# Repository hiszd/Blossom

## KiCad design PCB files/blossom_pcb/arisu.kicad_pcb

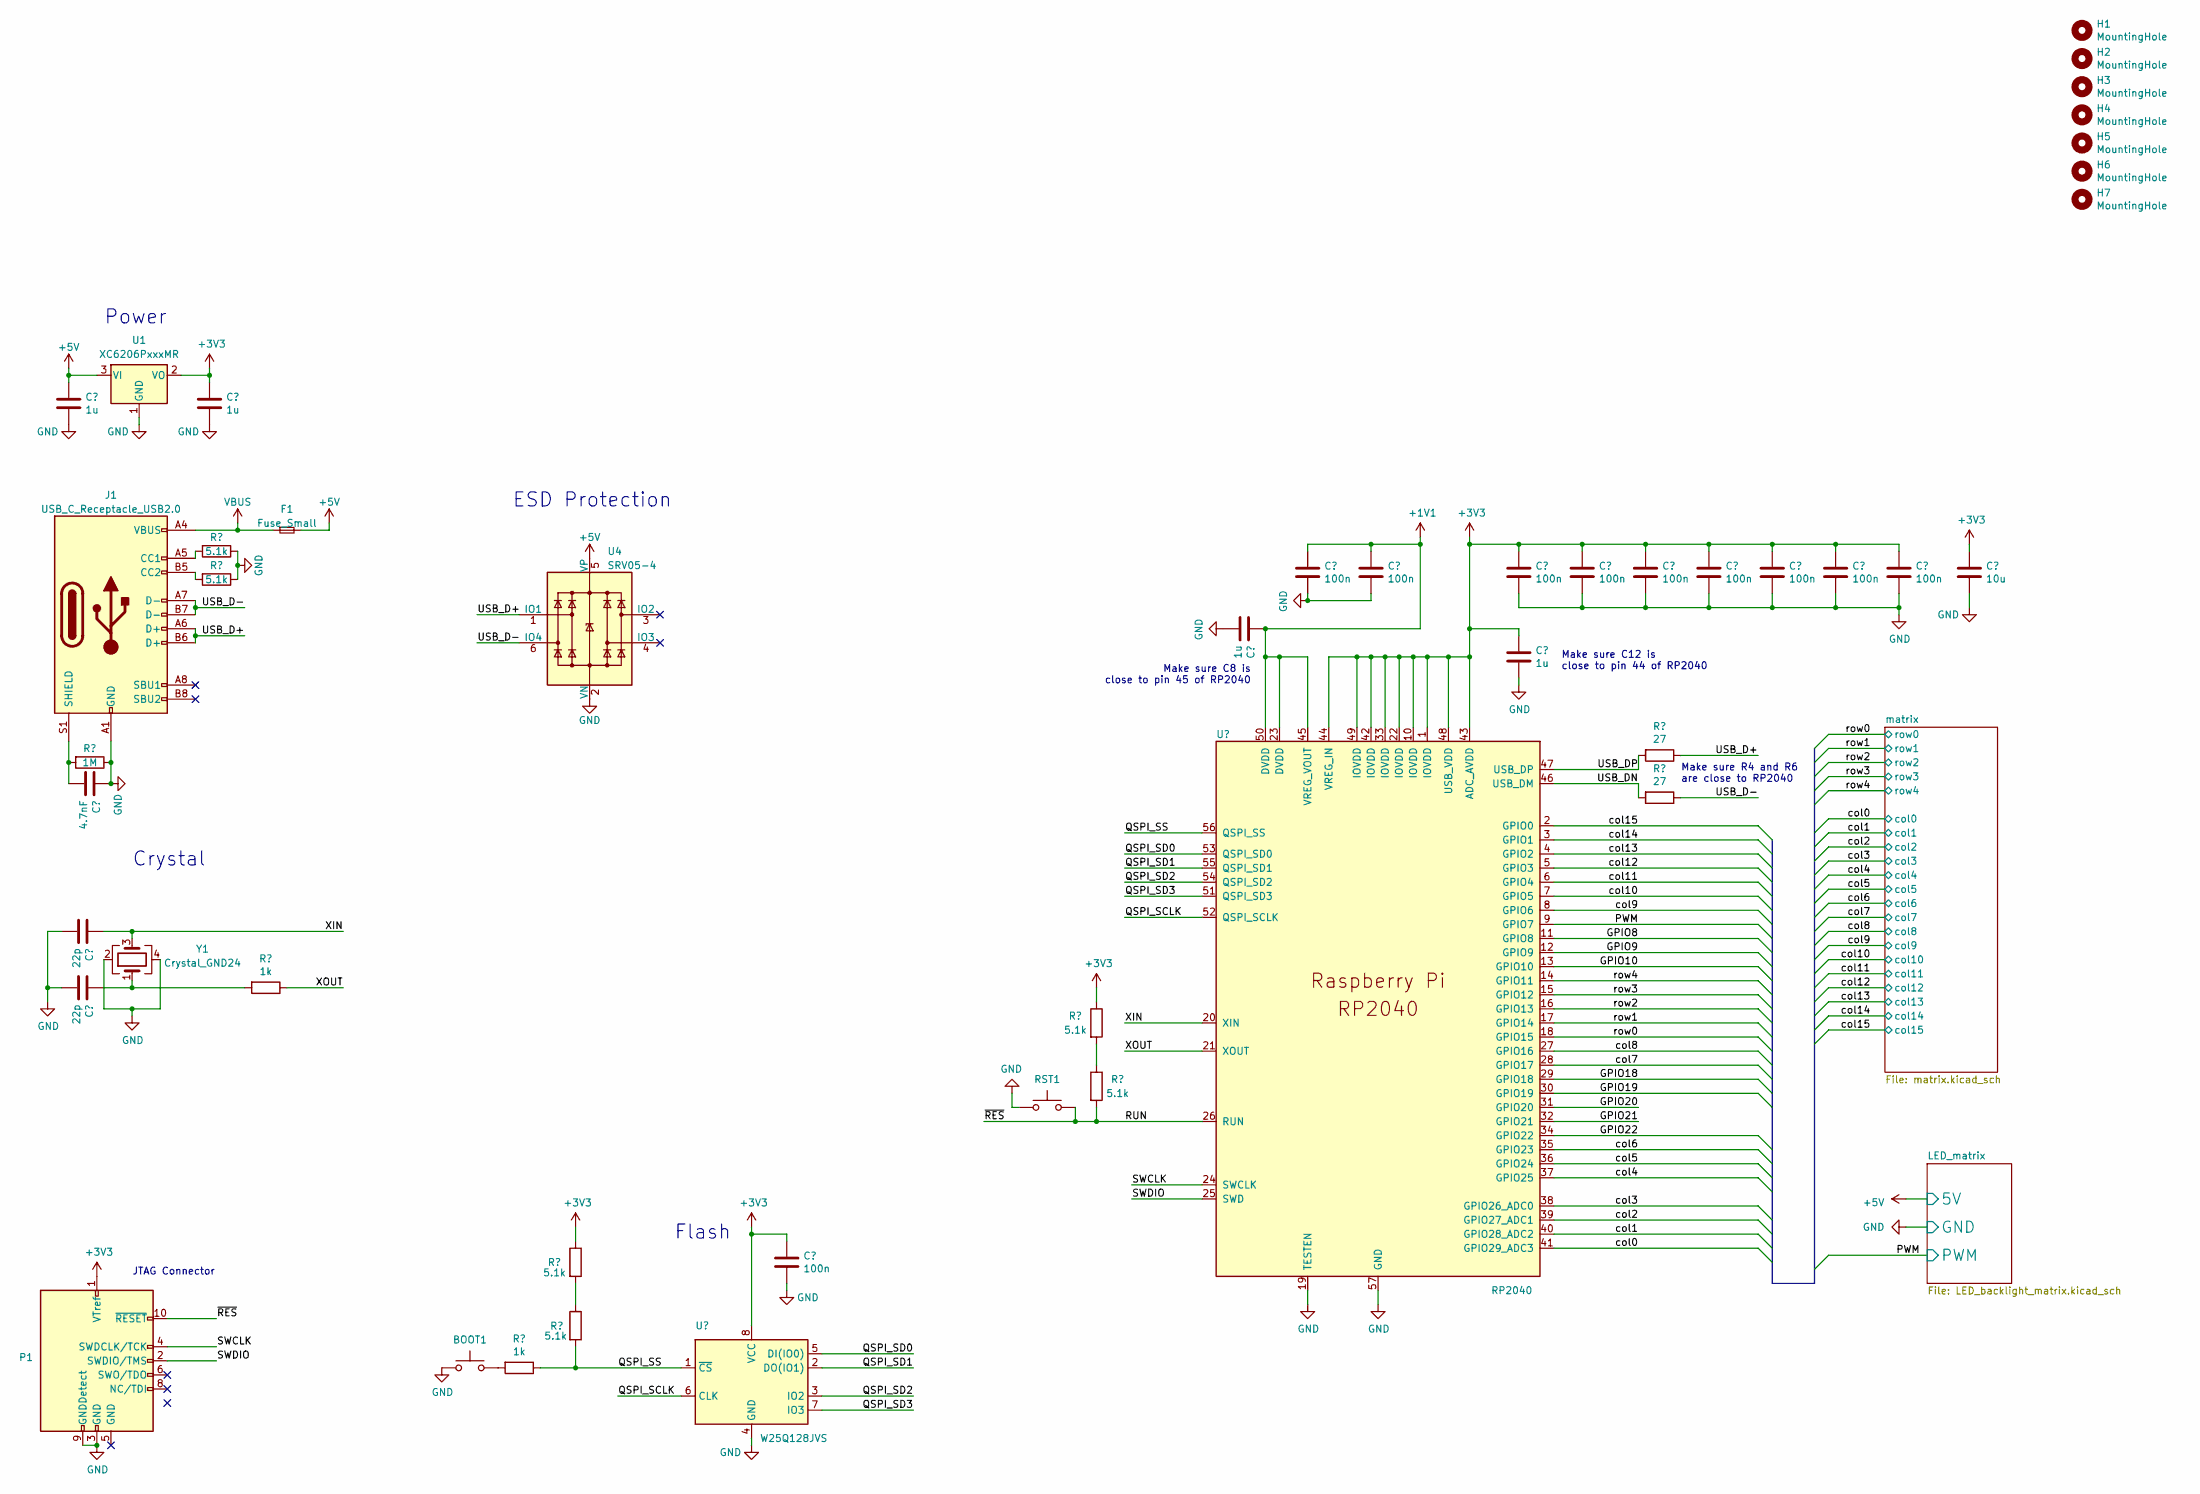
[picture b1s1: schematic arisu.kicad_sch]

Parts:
BOOT1: K2-6639DP-B4SW-04; SW_PUSH_6mm; LCSC C83205
C1, C2: 22p; C_0402_1005Metric
C3, C5, C8, C12: 1u; C_0402_1005Metric
C4, C6, C7, C9, C10, C11, C13, C14, C15, C16: 100n; C_0402_1005Metric
C17: 10u; C_0603_1608Metric
C18: 4.7nF; C_0402_1005Metric
F1: Fuse_Small; Fuse_1206_3216Metric; LCSC C20803
H1, H2, H3, H4, H5, H6, H7: MountingHole; MountingHole_2.2mm_M2_Pad
J1: USB_C_Receptacle_USB2.0; USB_C_Receptacle_HRO_TYPE-C-31-M-12; LCSC C165948
P1: Conn_ARM_JTAG_SWD_10; JLINK_NEEDLE
R1, R3: 1k; R_0402_1005Metric
R2, R4, R7, R8, R10, R11: 5.1k; R_0402_1005Metric
R5, R6: 27; R_0603_1608Metric
R9: 1M; R_0402_1005Metric
RST1: K2-6639DP-B4SW-04; SW_PUSH_6mm; LCSC C83205
U1: XC6206PxxxMR; SOT-23-3; LCSC C5250982
U2: W25Q128JVS; SOIC-8_5.23x5.23mm_P1.27mm
U3: RP2040; RP2040-QFN-56
U4: SRV05-4; SOT-23-6-routable; LCSC C85364
Y1: Crystal_GND24; Crystal_SMD_3225-4Pin_3.2x2.5mm; LCSC C9002

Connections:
+1V1: C6.1, C7.1, C8.1, U3.23 (DVDD), U3.45 (VREG_VOUT), U3.50 (DVDD)
+3V3: C4.1, C5.1, C9.1, C10.1, C11.1, C12.1, C13.1, C14.1, C15.1, C16.1, C17.1, P1.1 (VTref), R4.1, R10.1, U1.2 (VO), U2.8 (VCC), U3.1 (IOVDD), U3.10 (IOVDD), U3.22 (IOVDD), U3.33 (IOVDD), U3.42 (IOVDD), U3.43 (ADC_AVDD), U3.44 (VREG_IN), U3.48 (USB_VDD), U3.49 (IOVDD)
+5V: C3.1, F1.2, U1.3 (VI), U4.5 (VP); also elsewhere on the board
/GPIO8: U3.11 (GPIO8)
/GPIO9: U3.12 (GPIO9)
/GPIO10: U3.13 (GPIO10)
/GPIO18: U3.29 (GPIO18)
/GPIO19: U3.30 (GPIO19)
/GPIO20: U3.31 (GPIO20)
/GPIO21: U3.32 (GPIO21)
/GPIO22: U3.34 (GPIO22)
/PWM: U3.9 (GPIO7); also elsewhere on the board
/QSPI_SCLK: U2.6 (CLK), U3.52 (QSPI_SCLK)
/QSPI_SD0: U2.5 (DI(IO0)), U3.53 (QSPI_SD0)
/QSPI_SD1: U2.2 (DO(IO1)), U3.55 (QSPI_SD1)
/QSPI_SD2: U2.3 (IO2), U3.54 (QSPI_SD2)
/QSPI_SD3: U2.7 (IO3), U3.51 (QSPI_SD3)
/QSPI_SS: R1.1, R8.2, U2.1 (~CS), U3.56 (QSPI_SS)
/RUN: P1.10 (~RESET), R11.2, RST1.2, U3.26 (RUN)
/SWCLK: P1.4 (SWDCLK/TCK), U3.24 (SWCLK)
/SWDIO: P1.2 (SWDIO/TMS), U3.25 (SWD)
/USB_D+: J1.A6 (D+), J1.B6 (D+), R5.1, U4.1 (IO1)
/USB_D-: J1.A7 (D-), J1.B7 (D-), R6.1, U4.6 (IO4)
/USB_DN: R6.2, U3.46 (USB_DM)
/USB_DP: R5.2, U3.47 (USB_DP)
/XIN: C1.1, U3.20 (XIN), Y1.3
/XOUT: R3.1, U3.21 (XOUT)
/col0: U3.41 (GPIO29_ADC3); also elsewhere on the board
/col1: U3.40 (GPIO28_ADC2); also elsewhere on the board
/col2: U3.39 (GPIO27_ADC1); also elsewhere on the board
/col3: U3.38 (GPIO26_ADC0); also elsewhere on the board
/col4: U3.37 (GPIO25); also elsewhere on the board
/col5: U3.36 (GPIO24); also elsewhere on the board
/col6: U3.35 (GPIO23); also elsewhere on the board
/col7: U3.28 (GPIO17); also elsewhere on the board
/col8: U3.27 (GPIO16); also elsewhere on the board
/col9: U3.8 (GPIO6); also elsewhere on the board
/col10: U3.7 (GPIO5); also elsewhere on the board
/col11: U3.6 (GPIO4); also elsewhere on the board
/col12: U3.5 (GPIO3); also elsewhere on the board
/col13: U3.4 (GPIO2); also elsewhere on the board
/col14: U3.3 (GPIO1); also elsewhere on the board
/col15: U3.2 (GPIO0); also elsewhere on the board
/row0: U3.18 (GPIO15); also elsewhere on the board
/row1: U3.17 (GPIO14); also elsewhere on the board
/row2: U3.16 (GPIO13); also elsewhere on the board
/row3: U3.15 (GPIO12); also elsewhere on the board
/row4: U3.14 (GPIO11); also elsewhere on the board
GND: BOOT1.1, C1.2, C2.2, C3.2, C4.2, C5.2, C6.2, C7.2, C8.2, C9.2, C10.2, C11.2, C12.2, C13.2, C14.2, C15.2, C16.2, C17.2, C18.1, J1.A1 (GND), J1.A12 (GND), J1.B1 (GND), J1.B12 (GND), P1.3 (GND), P1.9 (GNDDetect), R2.1, R7.1, R9.1, RST1.1, U1.1 (GND), U2.4 (GND), U3.19 (TESTEN), U3.57 (GND), U4.2 (VN), Y1.2, Y1.4; also elsewhere on the board
unnamed: BOOT1.2, R1.2
unnamed: C2.1, R3.2, Y1.1
unnamed: J1.A5 (CC1), R2.2
unnamed: J1.B5 (CC2), R7.2
unnamed: C18.2, J1.S1 (SHIELD), R9.2
unnamed: R8.1, R10.2
unnamed: R4.2, R11.1
VBUS: F1.1, J1.A4 (VBUS), J1.A9 (VBUS), J1.B4 (VBUS), J1.B9 (VBUS)

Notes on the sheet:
Flash
JTAG Connector
Crystal
Make sure C8 is close to pin 45 of RP2040
ESD Protection
Make sure C12 is close to pin 44 of RP2040
Power
Make sure R4 and R6 are close to RP2040

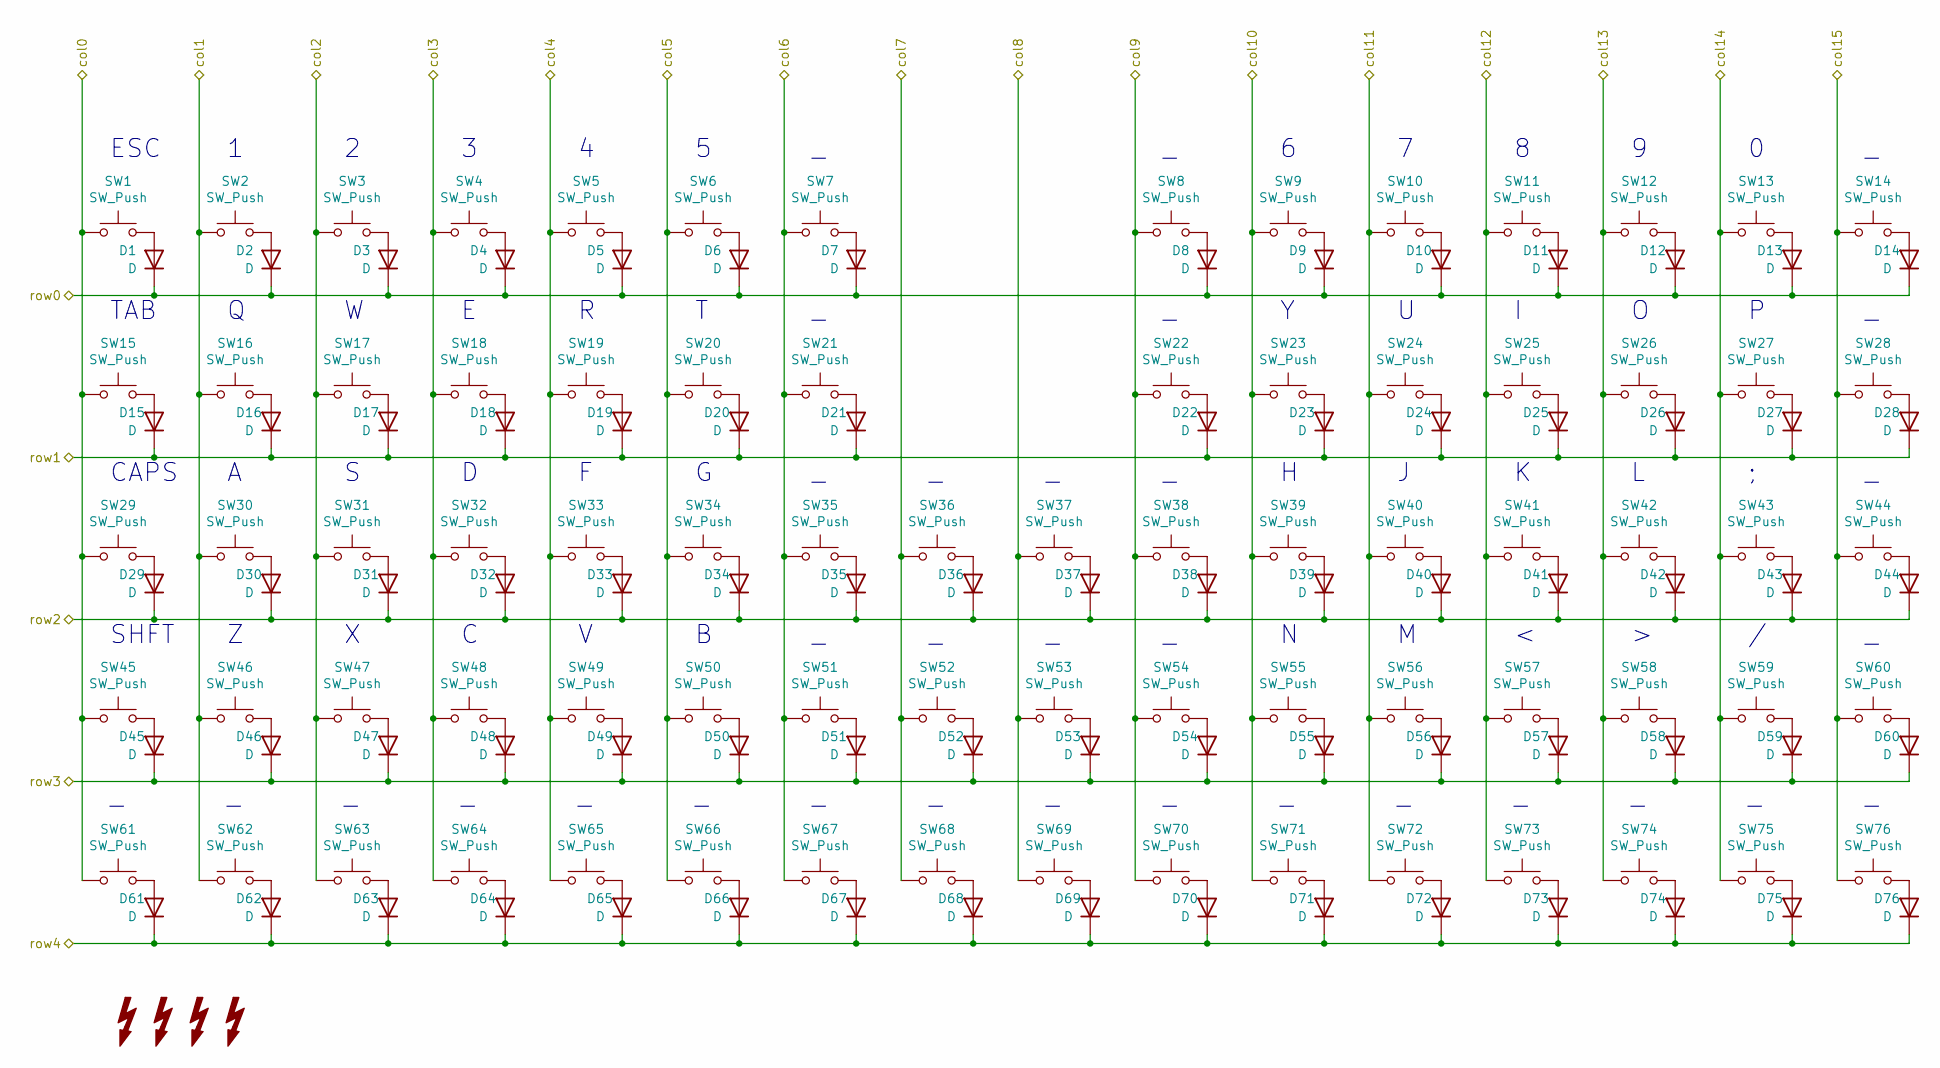
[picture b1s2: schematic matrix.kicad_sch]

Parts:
D1, D2, D3, D4, D5, D6, D7, D8, D9, D10, D11, D12, D13, D14, D15, D16, D17, D18, D19, D20, D21, D22, D23, D24, D25, D26, D27, D28, D29, D30, D31, D32, D33, D34, D35, D36, D37, D38, D39, D40, D41, D42, D43, D44, D45, D46, D47, D48, D49, D50, D51, D52, D53, D54, D55, D56, D57, D58, D59, D60, D61, D62, D63, D64, D65, D66, D67, D68, D69, D70, D71, D72, D73, D74, D75, D76: D; D_SOD-123; LCSC C2972762
SW1, SW2, SW3, SW4, SW5, SW6, SW7, SW8, SW9, SW10, SW11, SW12, SW13, SW14, SW15, SW16, SW17, SW18, SW19, SW20, SW21, SW22, SW23, SW24, SW25, SW26, SW27, SW28, SW29, SW30, SW31, SW32, SW33, SW34, SW35, SW38, SW39, SW40, SW41, SW42, SW43, SW44, SW45, SW46, SW47, SW48, SW49, SW50, SW52, SW53, SW55, SW56, SW57, SW58, SW59, SW60, SW61, SW62, SW63, SW64, SW65, SW66, SW67, SW68, SW69, SW70, SW71, SW72, SW73, SW74, SW75, SW76: SW_Push; SW_Hotswap_Kailh_MX_1.00u; LCSC C5156480
SW36, SW37, SW51, SW54: SW_Push; SW_Hotswap_Kailh_MX_2.00u; LCSC C5156480
SW36_Stab1, SW37_Stab1, SW51_Stab1, SW54_Stab1: Stabilizer_Cherry_MX_2.00u

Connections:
/col0: SW1.1, SW15.1, SW29.1, SW45.1, SW61.1; also elsewhere on the board
/col1: SW2.1, SW16.1, SW30.1, SW46.1, SW62.1; also elsewhere on the board
/col2: SW3.1, SW17.1, SW31.1, SW47.1, SW63.1; also elsewhere on the board
/col3: SW4.1, SW18.1, SW32.1, SW48.1, SW64.1; also elsewhere on the board
/col4: SW5.1, SW19.1, SW33.1, SW49.1, SW65.1; also elsewhere on the board
/col5: SW6.1, SW20.1, SW34.1, SW50.1, SW66.1; also elsewhere on the board
/col6: SW7.1, SW21.1, SW35.1, SW51.1, SW67.1; also elsewhere on the board
/col7: SW36.1, SW52.1, SW68.1; also elsewhere on the board
/col8: SW37.1, SW53.1, SW69.1; also elsewhere on the board
/col9: SW8.1, SW22.1, SW38.1, SW54.1, SW70.1; also elsewhere on the board
/col10: SW9.1, SW23.1, SW39.1, SW55.1, SW71.1; also elsewhere on the board
/col11: SW10.1, SW24.1, SW40.1, SW56.1, SW72.1; also elsewhere on the board
/col12: SW11.1, SW25.1, SW41.1, SW57.1, SW73.1; also elsewhere on the board
/col13: SW12.1, SW26.1, SW42.1, SW58.1, SW74.1; also elsewhere on the board
/col14: SW13.1, SW27.1, SW43.1, SW59.1, SW75.1; also elsewhere on the board
/col15: SW14.1, SW28.1, SW44.1, SW60.1, SW76.1; also elsewhere on the board
/row0: D1.1 (K), D2.1 (K), D3.1 (K), D4.1 (K), D5.1 (K), D6.1 (K), D7.1 (K), D8.1 (K), D9.1 (K), D10.1 (K), D11.1 (K), D12.1 (K), D13.1 (K), D14.1 (K); also elsewhere on the board
/row1: D15.1 (K), D16.1 (K), D17.1 (K), D18.1 (K), D19.1 (K), D20.1 (K), D21.1 (K), D22.1 (K), D23.1 (K), D24.1 (K), D25.1 (K), D26.1 (K), D27.1 (K), D28.1 (K); also elsewhere on the board
/row2: D29.1 (K), D30.1 (K), D31.1 (K), D32.1 (K), D33.1 (K), D34.1 (K), D35.1 (K), D36.1 (K), D37.1 (K), D38.1 (K), D39.1 (K), D40.1 (K), D41.1 (K), D42.1 (K), D43.1 (K), D44.1 (K); also elsewhere on the board
/row3: D45.1 (K), D46.1 (K), D47.1 (K), D48.1 (K), D49.1 (K), D50.1 (K), D51.1 (K), D52.1 (K), D53.1 (K), D54.1 (K), D55.1 (K), D56.1 (K), D57.1 (K), D58.1 (K), D59.1 (K), D60.1 (K); also elsewhere on the board
/row4: D61.1 (K), D62.1 (K), D63.1 (K), D64.1 (K), D65.1 (K), D66.1 (K), D67.1 (K), D68.1 (K), D69.1 (K), D70.1 (K), D71.1 (K), D72.1 (K), D73.1 (K), D74.1 (K), D75.1 (K), D76.1 (K); also elsewhere on the board
unnamed: D1.2 (A), SW1.2
unnamed: D2.2 (A), SW2.2
unnamed: D3.2 (A), SW3.2
unnamed: D4.2 (A), SW4.2
unnamed: D5.2 (A), SW5.2
unnamed: D6.2 (A), SW6.2
unnamed: D7.2 (A), SW7.2
unnamed: D8.2 (A), SW8.2
unnamed: D9.2 (A), SW9.2
unnamed: D10.2 (A), SW10.2
unnamed: D11.2 (A), SW11.2
unnamed: D12.2 (A), SW12.2
unnamed: D13.2 (A), SW13.2
unnamed: D14.2 (A), SW14.2
unnamed: D15.2 (A), SW15.2
unnamed: D16.2 (A), SW16.2
unnamed: D17.2 (A), SW17.2
unnamed: D18.2 (A), SW18.2
unnamed: D19.2 (A), SW19.2
unnamed: D20.2 (A), SW20.2
unnamed: D21.2 (A), SW21.2
unnamed: D22.2 (A), SW22.2
unnamed: D23.2 (A), SW23.2
unnamed: D24.2 (A), SW24.2
unnamed: D25.2 (A), SW25.2
unnamed: D26.2 (A), SW26.2
unnamed: D27.2 (A), SW27.2
unnamed: D28.2 (A), SW28.2
unnamed: D29.2 (A), SW29.2
unnamed: D30.2 (A), SW30.2
unnamed: D31.2 (A), SW31.2
unnamed: D32.2 (A), SW32.2
unnamed: D33.2 (A), SW33.2
unnamed: D34.2 (A), SW34.2
unnamed: D35.2 (A), SW35.2
unnamed: D36.2 (A), SW36.2
unnamed: D37.2 (A), SW37.2
unnamed: D38.2 (A), SW38.2
unnamed: D39.2 (A), SW39.2
unnamed: D40.2 (A), SW40.2
unnamed: D41.2 (A), SW41.2
unnamed: D42.2 (A), SW42.2
unnamed: D43.2 (A), SW43.2
unnamed: D44.2 (A), SW44.2
unnamed: D45.2 (A), SW45.2
unnamed: D46.2 (A), SW46.2
unnamed: D47.2 (A), SW47.2
unnamed: D48.2 (A), SW48.2
unnamed: D49.2 (A), SW49.2
unnamed: D50.2 (A), SW50.2
unnamed: D51.2 (A), SW51.2
unnamed: D52.2 (A), SW52.2
unnamed: D53.2 (A), SW53.2
unnamed: D54.2 (A), SW54.2
unnamed: D55.2 (A), SW55.2
unnamed: D56.2 (A), SW56.2
unnamed: D57.2 (A), SW57.2
unnamed: D58.2 (A), SW58.2
unnamed: D59.2 (A), SW59.2
unnamed: D60.2 (A), SW60.2
unnamed: D61.2 (A), SW61.2
unnamed: D62.2 (A), SW62.2
unnamed: D63.2 (A), SW63.2
unnamed: D64.2 (A), SW64.2
unnamed: D65.2 (A), SW65.2
unnamed: D66.2 (A), SW66.2
unnamed: D67.2 (A), SW67.2
unnamed: D68.2 (A), SW68.2
unnamed: D69.2 (A), SW69.2
unnamed: D70.2 (A), SW70.2
unnamed: D71.2 (A), SW71.2
unnamed: D72.2 (A), SW72.2
unnamed: D73.2 (A), SW73.2
unnamed: D74.2 (A), SW74.2
unnamed: D75.2 (A), SW75.2
unnamed: D76.2 (A), SW76.2

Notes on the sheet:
SHFT
ESC
CAPS
TAB

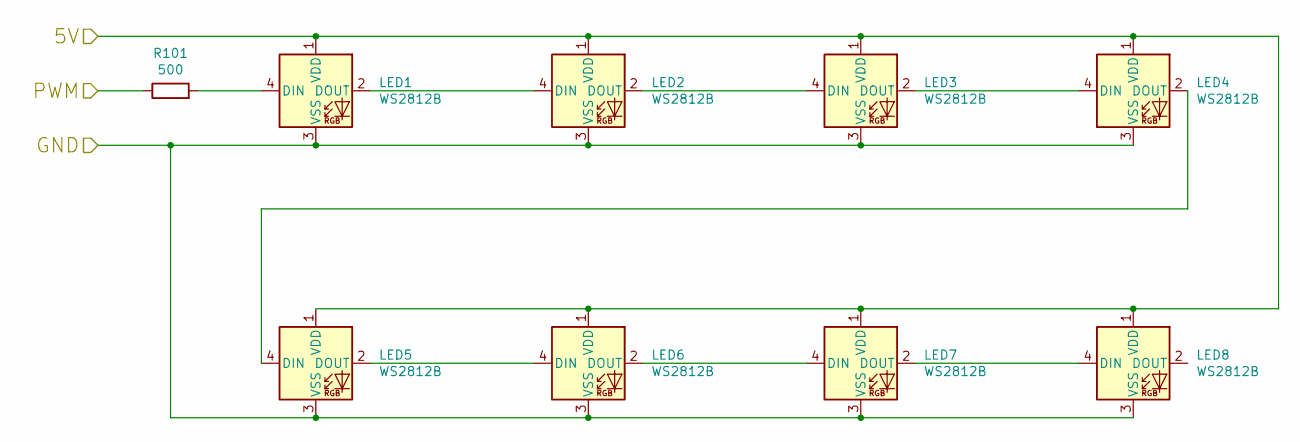
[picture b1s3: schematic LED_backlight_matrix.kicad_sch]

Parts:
LED1, LED2, LED3, LED4, LED5, LED6, LED7, LED8: WS2812B; LED_WS2812B_PLCC4_5.0x5.0mm_P3.2mm
R101: 500; R_0805_2012Metric

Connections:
+5V: LED1.1 (VDD), LED2.1 (VDD), LED3.1 (VDD), LED4.1 (VDD), LED5.1 (VDD), LED6.1 (VDD), LED7.1 (VDD), LED8.1 (VDD); also elsewhere on the board
/PWM: R101.1; also elsewhere on the board
GND: LED1.3 (VSS), LED2.3 (VSS), LED3.3 (VSS), LED4.3 (VSS), LED5.3 (VSS), LED6.3 (VSS), LED7.3 (VSS), LED8.3 (VSS); also elsewhere on the board
unnamed: LED1.4 (DIN), R101.2
unnamed: LED1.2 (DOUT), LED2.4 (DIN)
unnamed: LED2.2 (DOUT), LED3.4 (DIN)
unnamed: LED3.2 (DOUT), LED4.4 (DIN)
unnamed: LED4.2 (DOUT), LED5.4 (DIN)
unnamed: LED5.2 (DOUT), LED6.4 (DIN)
unnamed: LED6.2 (DOUT), LED7.4 (DIN)
unnamed: LED7.2 (DOUT), LED8.4 (DIN)

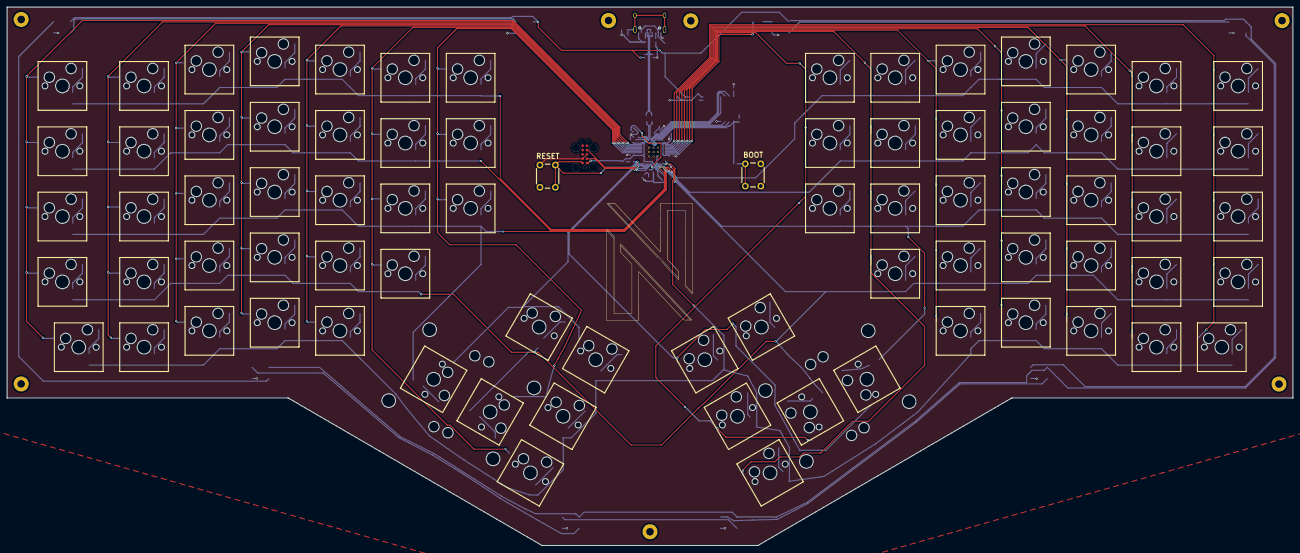
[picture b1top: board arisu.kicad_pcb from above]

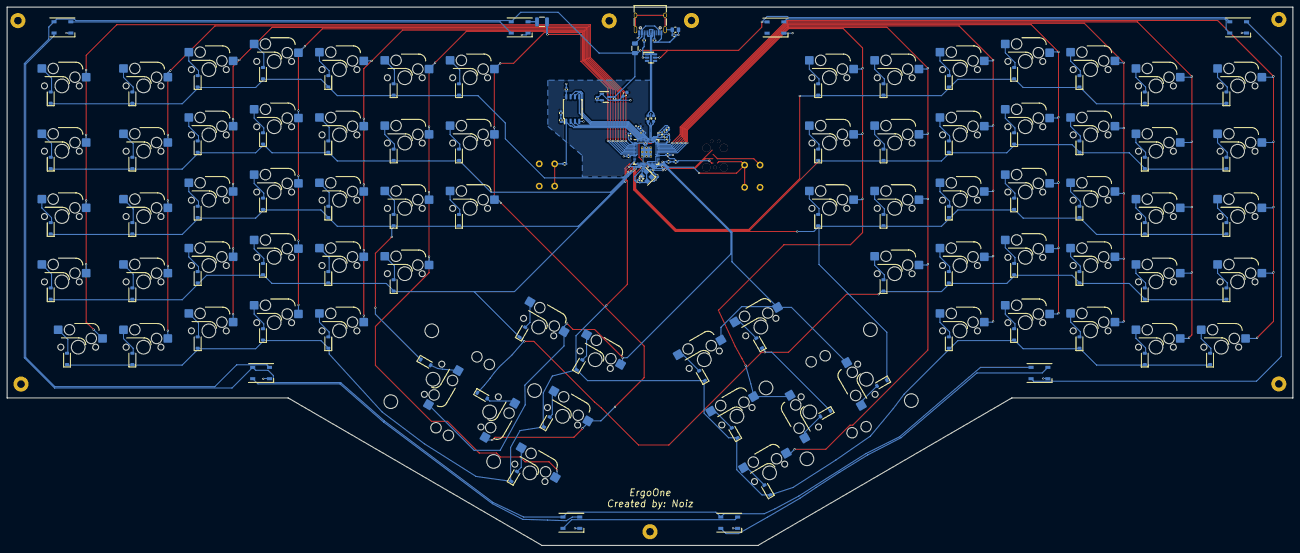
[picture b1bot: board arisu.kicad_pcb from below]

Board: 2 copper layers, 375.0 x 157.0 mm, 207 parts (197 on the bottom side), 133 nets.

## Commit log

2023-05-22 Adding rp2040 to schematic
2023-05-23 added rp2040, need to update footprints
2023-05-24 Almost doing stuffs
2023-05-24 diodes placed
2023-05-24 Almost complete
2023-05-25 Everything is connected
2023-05-25 Adjusted rp2040 layout and changed pin assignments
2023-05-26 Better traces.
2023-05-26 probably final without usb
2023-05-30 Added usb
2023-05-31 lots of stuff
2023-05-31 Cleanup
2023-06-01 Added solidworks files
2023-06-01 Fixed part numbers for JLCPCB
2023-06-02 stuff
2023-06-02 Possible final
2023-06-03 Final Prototype 1
2023-06-05 New model and "final" pcb
2023-06-05 updated 3d design
2023-06-05 almost wristrest
2023-06-05 Final case first prototype
2023-06-05 First case proto
2023-06-05 iter1
2023-06-06 Fixed PCB for LEDs and R9
2023-06-07 final for real
